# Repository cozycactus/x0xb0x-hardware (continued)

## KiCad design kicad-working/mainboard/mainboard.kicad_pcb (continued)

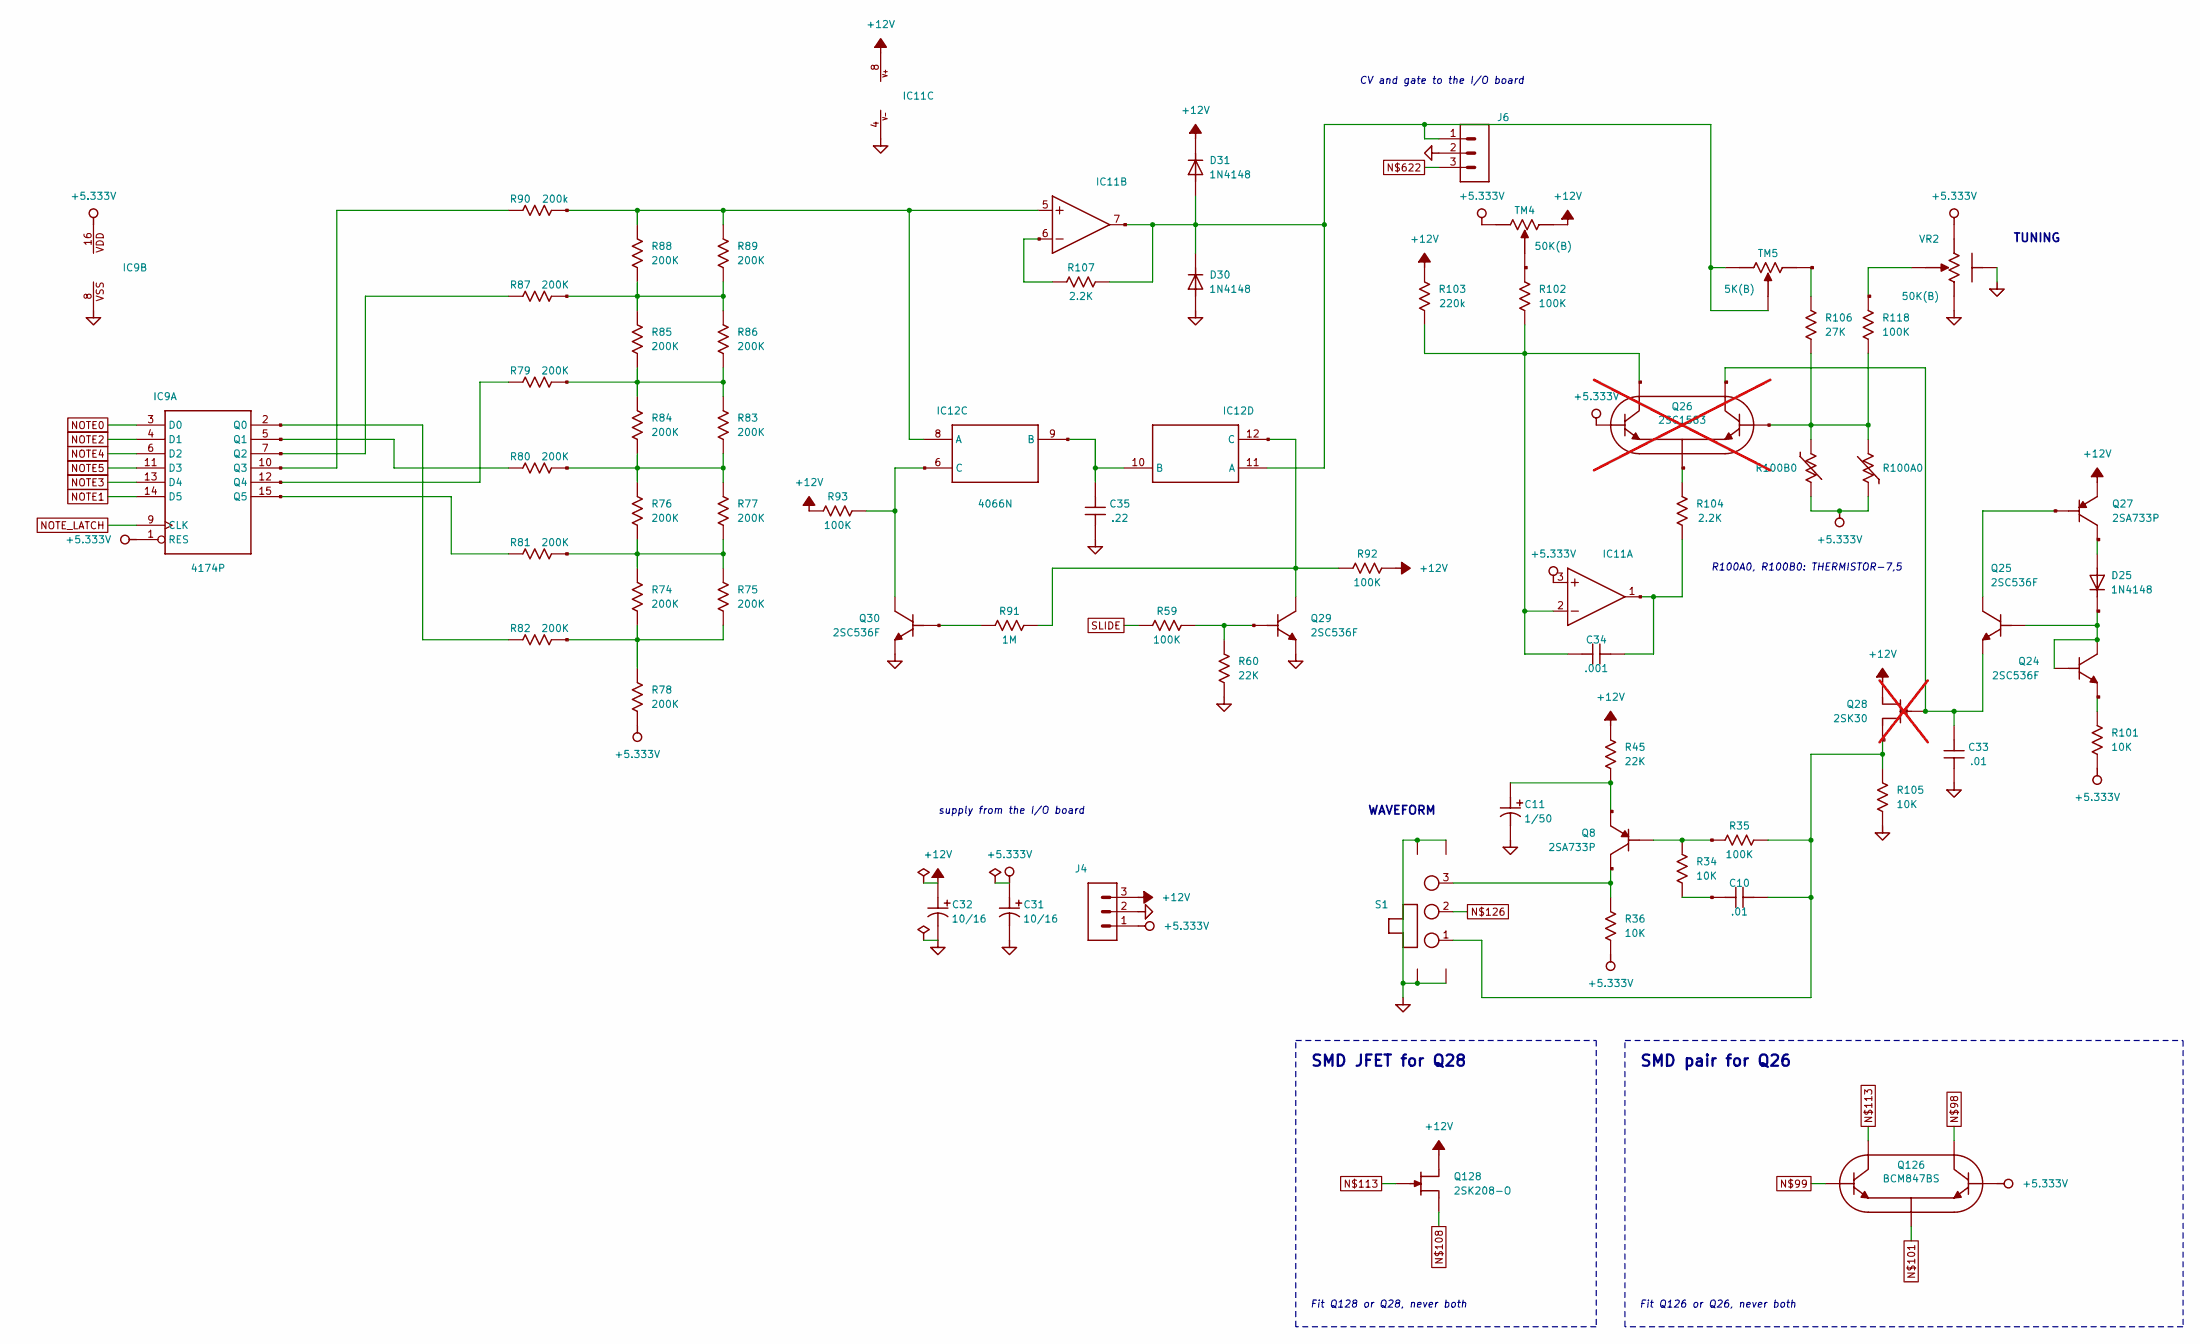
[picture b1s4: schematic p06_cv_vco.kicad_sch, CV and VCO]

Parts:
C10, C33: .01; C050-024X044
C11: 1/50; E5-6
C31, C32: 10/16; E5-6
C34: .001; C050-035X075
C35: .22; C050-045X075
D25, D30, D31: 1N4148; DO35-10
IC9: 4174P; DIL16
IC11: AN656N; DIL08
IC12: 4066N; DIL14
J4, J6: MA03-''; MA03-1
Q8, Q27: 2SA733P; TO92
Q24, Q25, Q29, Q30: 2SC536F
Q26: 2SC1583; SSIP5; not fitted
Q28: 2SK30; not fitted
Q126: BCM847BS; SOT-363_Hand
Q128: 2SK208-O; SC-59_Hand
R34, R36, R101, R105: 10K; 0207_5V
R35, R59, R92, R93, R102, R118: 100K; 0207_5V
R45, R60: 22K; 0207_5V
R74, R75, R76, R77, R78, R79, R80, R81, R82, R83, R84, R85, R86, R87, R88, R89: 200K; 0207_5V
R90: 200k; 0207_5V
R91: 1M; 0207_5V
R100A0, R100B0: THERMISTOR-7,5; R-7,5
R103: 220k; 0207_5V
R104, R107: 2.2K; 0207_5V
R106: 27K; 0207_5V
S1: SWITCH_GND; NKKTOGGLE
TM4: 50K(B); 306
TM5: 5K(B); 306
VR2: 50K(B); EVU

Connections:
+5.333V: C31.+, IC9.1 (RES), IC9.16 (VDD), IC11.3 (+IN), J4.1, Q26.1 (B), Q126.2 (B1), R36.2, R78.1, R100A0.2, R100B0.1, R101.2, TM4.3 (E), VR2.3 (E); also elsewhere on the board
+12V: C32.+, D31.C, IC11.8 (V+), J4.3, Q27.3 (E), Q28.1 (D), Q128.2 (D), R45.1, R92.2, R93.1, R103.1, TM4.1 (A); also elsewhere on the board
GND: C11.-, C31.-, C32.-, C33.2, C35.2, D30.A, IC9.8 (VSS), IC11.4 (V-), J4.2, J6.2, Q29.3 (E), Q30.3 (E), R60.1, R105.1, S1.M1, S1.M2, S1.M3, S1.M4, VR2.1 (A), VR2.M1, VR2.M2; also elsewhere on the board
unnamed: IC9.10 (Q3), R90.1
unnamed: C35.1, IC12.9 (B), IC12.10 (B)
unnamed: IC12.6 (C), Q30.2 (C), R93.2
unnamed: Q30.1 (B), R91.2
unnamed: IC11.6 (-IN), R107.1
unnamed: R85.2, R86.1, R87.2, R88.2, R89.1
unnamed: IC12.12 (C), Q29.2 (C), R91.1, R92.1
unnamed: R79.1, R83.1, R84.2, R85.1, R86.2
unnamed: IC9.15 (Q5), R81.2
unnamed: IC9.2 (Q0), R82.1
unnamed: IC9.12 (Q4), R79.2
unnamed: Q29.1 (B), R59.2, R60.2
unnamed: C34.1, IC11.1 (OUT), R104.2
unnamed: C34.2, IC11.2 (-IN), Q26.2 (C), Q126.6 (C1), R102.1, R103.2
unnamed: Q26.5 (B1), Q126.5 (B), R100A0.1, R100B0.2, R106.2, R118.2
unnamed: Q26.3 (E), Q126.1 (E), Q126.4 (E1), R104.1
unnamed: R118.1, VR2.2 (S)
unnamed: D25.A, Q27.2 (C)
unnamed: D25.C, Q24.1 (B), Q24.2 (C), Q25.1 (B)
unnamed: Q24.3 (E), R101.1
unnamed: Q25.2 (C), Q27.1 (B)
unnamed: C10.1, Q28.3 (S), Q128.1 (S), R35.1, R105.2, S1.1
unnamed: Q8.1 (B), R34.1, R35.2
unnamed: C10.2, R34.2
unnamed: IC11.5 (+IN), IC12.8 (A), R88.1, R89.2, R90.2
unnamed: C33.1, Q25.3 (E), Q26.4 (C1), Q28.2 (G), Q126.3 (C), Q128.3 (G)
unnamed: R102.2, TM4.2 (S)
unnamed 125: S1.2; also elsewhere on the board
unnamed: R76.2, R77.1, R80.2, R83.2, R84.1
unnamed: R106.1, TM5.1 (A)
unnamed: IC9.7 (Q2), R87.1
unnamed: IC9.5 (Q1), R80.1
unnamed: R74.2, R75.2, R78.2, R82.2
unnamed: R74.1, R75.1, R76.1, R77.2, R81.1
unnamed: C11.+, Q8.3 (E), R45.2
unnamed: Q8.2 (C), R36.1, S1.3
unnamed 297: J6.3; also elsewhere on the board
unnamed: D30.C, D31.A, IC11.7 (OUT), IC12.11 (A), J6.1, R107.2, TM5.2 (S), TM5.3 (E)
NOTE0: IC9.3 (D0); also elsewhere on the board
NOTE1: IC9.14 (D5); also elsewhere on the board
NOTE2: IC9.4 (D1); also elsewhere on the board
NOTE3: IC9.13 (D4); also elsewhere on the board
NOTE4: IC9.6 (D2); also elsewhere on the board
NOTE5: IC9.11 (D3); also elsewhere on the board
NOTE_LATCH: IC9.9 (CLK); also elsewhere on the board
SLIDE: R59.1; also elsewhere on the board

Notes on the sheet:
TUNING
R100A0, R100B0: THERMISTOR-7,5
WAVEFORM
supply from the I/O board
CV and gate to the I/O board
SMD pair for Q26
Fit Q126 or Q26, never both
SMD JFET for Q28
Fit Q128 or Q28, never both

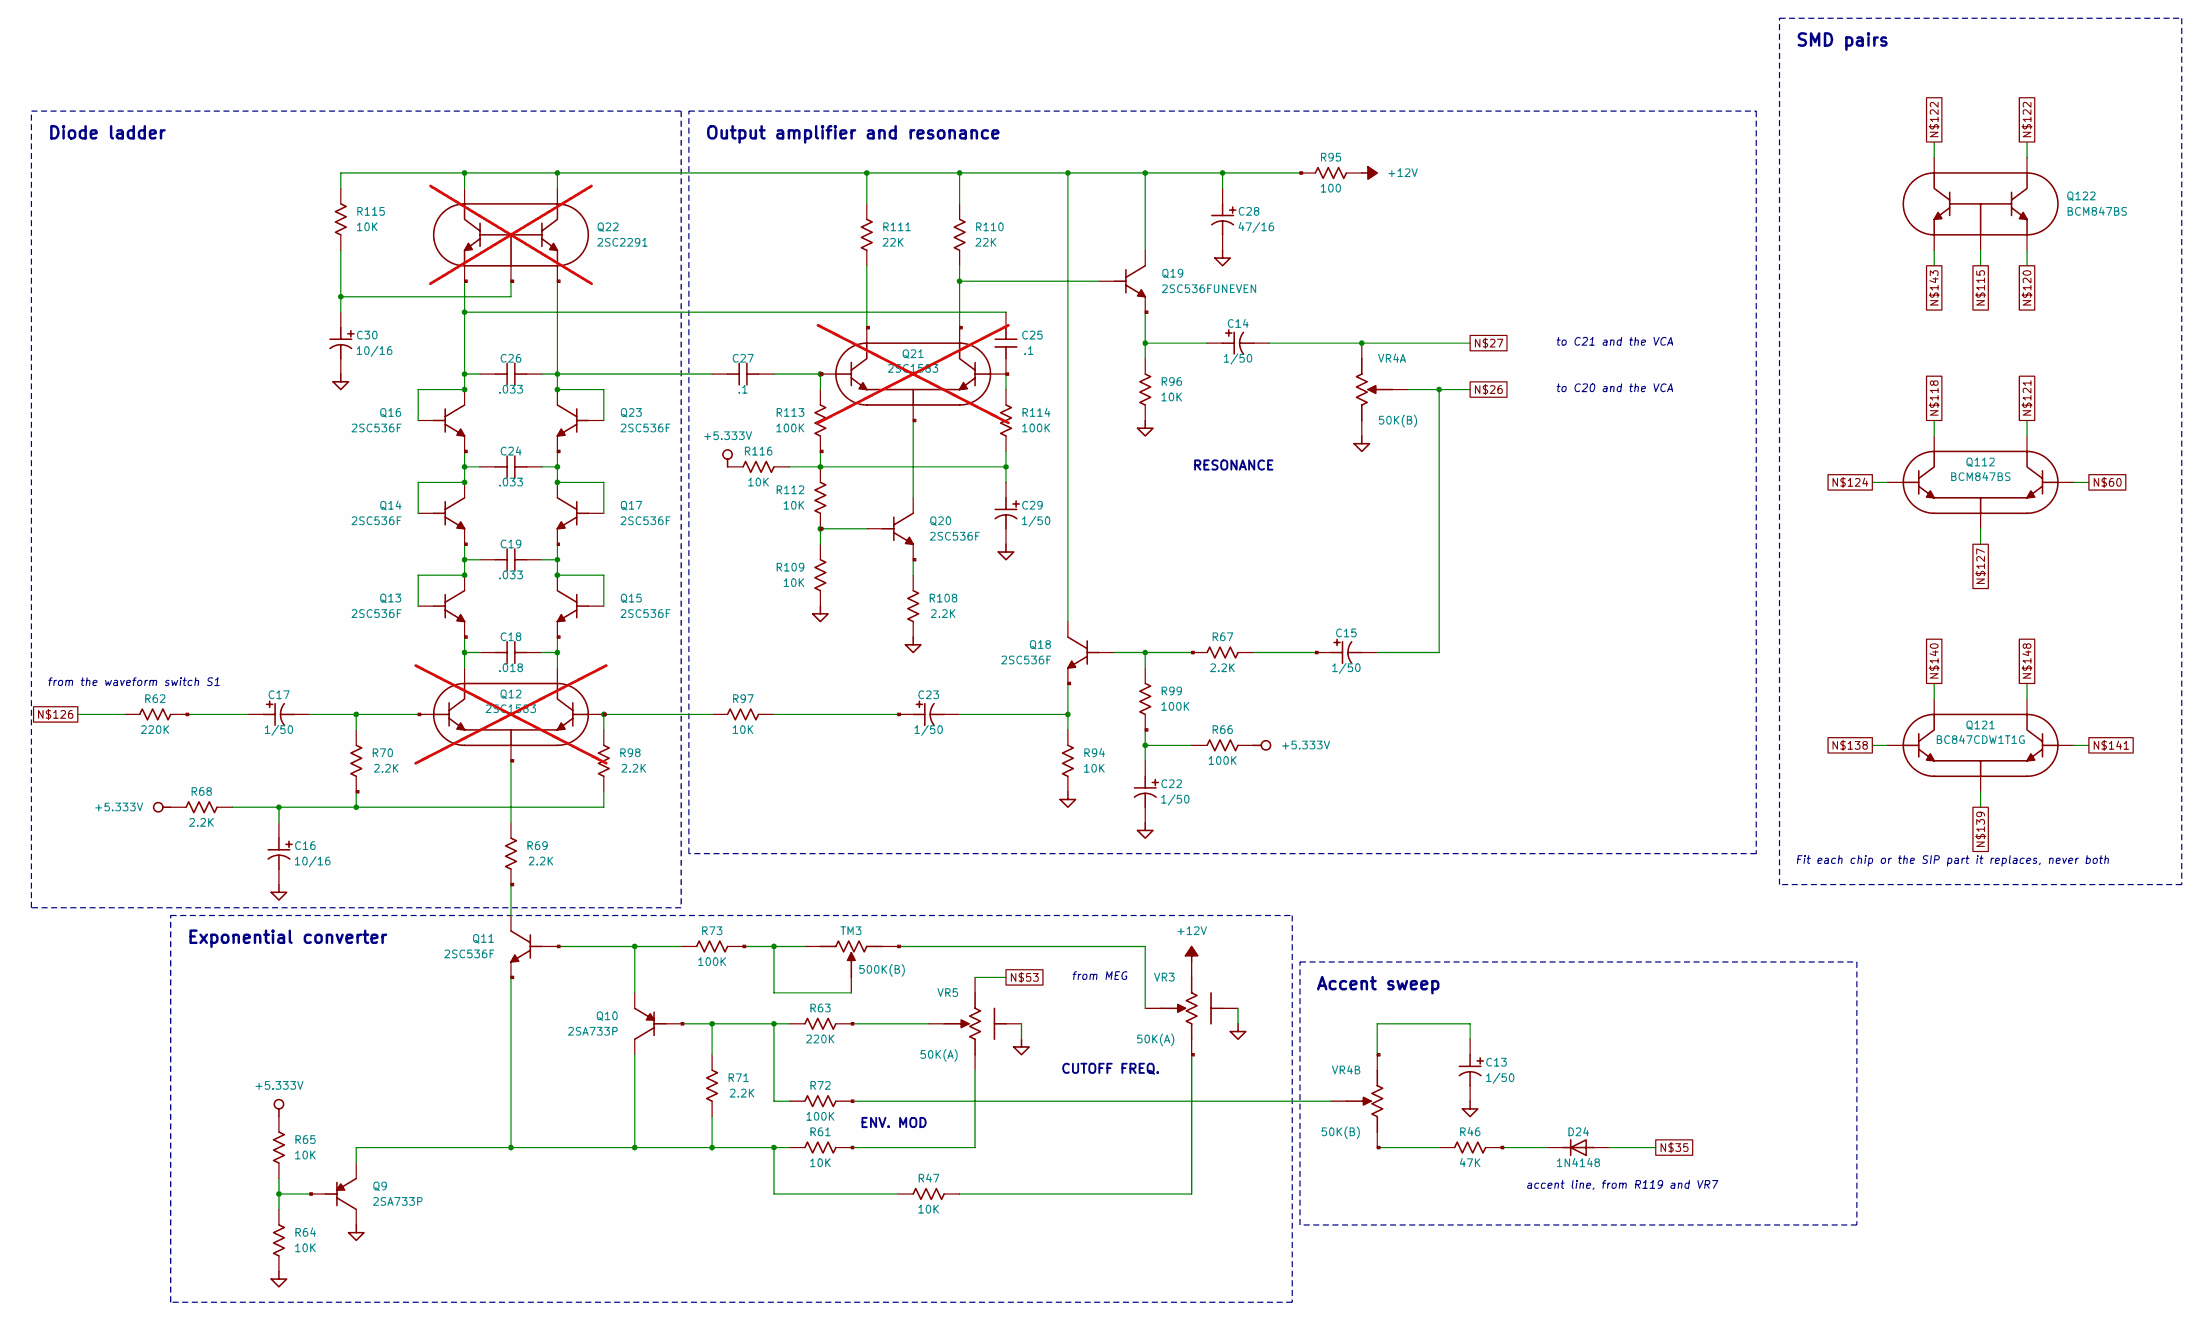
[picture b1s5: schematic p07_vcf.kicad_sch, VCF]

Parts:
C13, C14, C15, C22, C23, C29: 1/50; E5-6
C16, C30: 10/16; E5-6
C17: 1/50; E3,5-8
C18: .018; C050-025X075
C19, C24: .033; C050-025X075
C25, C27: .1; C050-030X075
C26: .033; C075-032X103
C28: 47/16; E5-6
D24: 1N4148; DO35-10
Q9, Q10: 2SA733P; TO92
Q11, Q13, Q14, Q15, Q16, Q18, Q20: 2SC536F
Q12, Q21: 2SC1583; SSIP5; not fitted
Q17, Q23: 2SC536F; 2SC536_UNEVEN
Q19: 2SC536FUNEVEN; 2SC536_UNEVEN
Q22: 2SC2291; SSIP5; not fitted
Q112, Q122: BCM847BS; SOT-363_Hand
Q121: BC847CDW1T1G; SOT-363_Hand
R46: 47K; 0207_5V
R47, R61, R64, R65, R94, R109, R112, R116: 10K; 0207_5V
R62, R63: 220K; 0207_5V
R66, R72, R73, R99, R113, R114: 100K; 0207_5V
R67, R68, R69, R70, R71, R108: 2.2K; 0207_5V
R95: 100; 0207_5V
R96, R97, R115: 10K; 0207_2V
R98: 2.2K; 0207_2V
R110, R111: 22K; 0207_5V
TM3: 500K(B); 306
VR3, VR5: 50K(A); EVU
VR4: 50K(B); ALPHADUAL

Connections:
+5.333V: R65.2, R66.2, R68.1, R116.2; also elsewhere on the board
+12V: R95.2, VR3.3 (E); also elsewhere on the board
GND: C13.-, C16.-, C22.-, C28.-, C29.-, C30.-, Q9.2 (C), R64.2, R94.1, R96.1, R108.1, R109.2, VR3.M1, VR3.M2, VR4.1A (A), VR4.M1 (MT1), VR4.M2 (MT2), VR5.M1, VR5.M2; also elsewhere on the board
unnamed 40: C15.-, VR4.2A (S); also elsewhere on the board
unnamed 41: C14.-, VR4.3A (E); also elsewhere on the board
unnamed 49: D24.A; also elsewhere on the board
unnamed: R61.1, VR5.1 (A)
unnamed 66: VR5.3 (E); also elsewhere on the board
unnamed: Q12.5 (B1), Q112.2 (B1), R97.1, R98.1
unnamed: C30.+, Q22.3 (B), Q122.2 (B), Q122.5 (B1), R115.2
unnamed: C24.1, Q14.1 (B), Q14.2 (C), Q16.3 (E)
unnamed: C19.1, Q13.1 (B), Q13.2 (C), Q14.3 (E)
unnamed: C18.2, Q12.2 (C), Q13.3 (E), Q112.3 (C)
unnamed: C24.2, Q17.1 (B), Q17.2 (C), Q23.3 (E)
unnamed: C26.2, C27.1, Q22.5 (E), Q23.1 (B), Q23.2 (C), Q122.1 (E)
unnamed: C18.1, Q12.4 (C1), Q15.3 (E), Q112.6 (C1)
unnamed: C28.+, Q18.2 (C), Q19.2 (C), Q22.2 (C1), Q22.4 (C), Q122.3 (C1), Q122.6 (C), R95.1, R110.2, R111.1, R115.1
unnamed: C17.+, R62.2
unnamed: C17.-, Q12.1 (B), Q112.5 (B), R70.1
unnamed: C16.+, R68.2, R70.2, R98.2
unnamed 125: R62.1; also elsewhere on the board
unnamed: Q12.3 (E), Q112.1 (E), Q112.4 (E1), R69.1
unnamed: C23.+, R97.2
unnamed: C23.-, Q18.3 (E), R94.2
unnamed: Q18.1 (B), R67.2, R99.2
unnamed: C22.+, R66.1, R99.1
unnamed: C15.+, R67.1
unnamed: Q10.1 (B), R63.1, R71.2, R72.1
unnamed: Q20.1 (B), R109.1, R112.2
unnamed: Q20.3 (E), R108.2
unnamed: C25.2, Q21.1 (B), Q121.5 (B), R114.2
unnamed: Q20.2 (C), Q21.3 (E), Q121.1 (E), Q121.4 (E1)
unnamed: Q19.1 (B), Q21.2 (C), Q121.3 (C), R110.1
unnamed: C27.2, Q21.5 (B1), Q121.2 (B1), R113.1
unnamed: R47.1, VR3.1 (A)
unnamed: C25.1, C26.1, Q16.1 (B), Q16.2 (C), Q22.1 (E1), Q122.4 (E1)
unnamed: C14.+, Q19.3 (E), R96.2
unnamed: Q11.2 (C), R69.2
unnamed: Q10.3 (E), Q11.1 (B), R73.1
unnamed: Q21.4 (C1), Q121.6 (C1), R111.2
unnamed: Q9.1 (B), R64.1, R65.1
unnamed: R73.2, TM3.2 (S), TM3.3 (E)
unnamed: R72.2, VR4.2B (S1)
unnamed: R63.2, VR5.2 (S)
unnamed: TM3.1 (A), VR3.2 (S)
unnamed: D24.C, R46.1
unnamed: R46.2, VR4.1B (A1)
unnamed: C13.+, VR4.3B (E1)
unnamed: Q9.3 (E), Q10.2 (C), Q11.3 (E), R47.2, R61.2, R71.1
unnamed: C29.+, R112.1, R113.2, R114.1, R116.1
Q17: C19.2, Q15.1 (B), Q15.2 (C), Q17.3 (E)

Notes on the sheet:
Diode ladder
Output amplifier and resonance
Exponential converter
Accent sweep
from the waveform switch S1
to C21 and the VCA
to C20 and the VCA
RESONANCE
from MEG
ENV. MOD
CUTOFF FREQ.
accent line, from R119 and VR7
SMD pairs
Fit each chip or the SIP part it replaces, never both

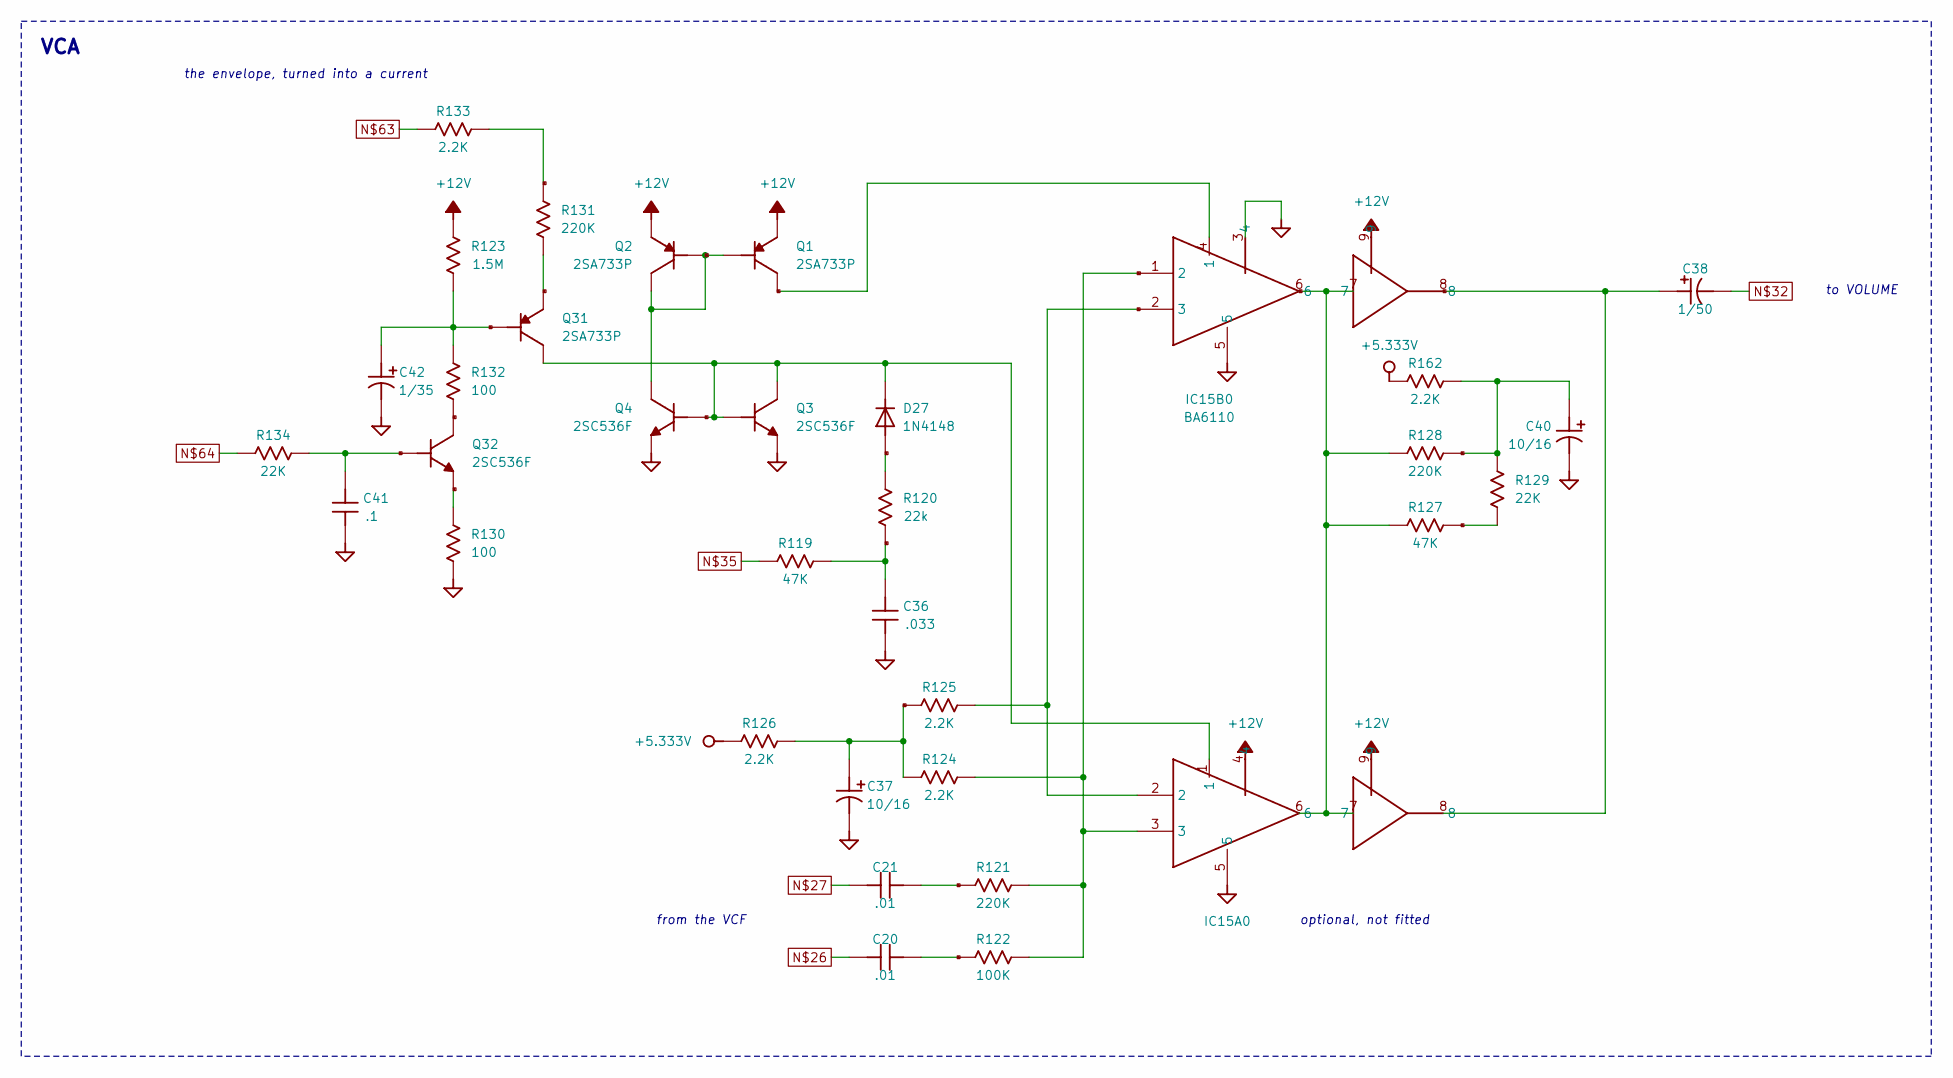
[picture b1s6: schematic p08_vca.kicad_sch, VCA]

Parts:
C20, C21: .01; C050-024X044
C36: .033; C050-025X075
C37, C40: 10/16; E5-6
C38: 1/50; E5-6
C41: .1; C050-030X075
C42: 1/35; E2,5-7
D27: 1N4148; DO35-10
IC15A0: BA662''; SIP9
IC15B0: BA6110; SIP9
Q1, Q2, Q31: 2SA733P; TO92
Q3, Q4, Q32: 2SC536F
R119, R127: 47K; 0207_5V
R120: 22k; 0207_5V
R121, R128, R131: 220K; 0207_5V
R122: 100K; 0207_5V
R123: 1.5M; 0207_5V
R124, R125, R126, R133, R162: 2.2K; 0207_5V
R129, R134: 22K; 0207_5V
R130, R132: 100; 0207_5V

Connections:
+5.333V: R126.1, R162.1; also elsewhere on the board
+12V: IC15A0.4, IC15A0.9, IC15B0.9, Q1.3 (E), Q2.3 (E), R123.2; also elsewhere on the board
GND: C36.2, C37.-, C40.-, C41.2, C42.-, IC15A0.5, IC15B0.3 (4), IC15B0.5, Q3.3 (E), Q4.3 (E), R130.2; also elsewhere on the board
unnamed: C20.1, R122.2
unnamed: C37.+, R124.2, R125.1, R126.2
unnamed: IC15A0.2, IC15B0.2 (3), R125.2
unnamed: C21.1, R121.1
unnamed 40: C20.2; also elsewhere on the board
unnamed 41: C21.2; also elsewhere on the board
unnamed: IC15A0.6, IC15A0.7, IC15B0.6, IC15B0.7, R127.1, R128.2
unnamed: IC15B0.4 (1), Q1.2 (C)
unnamed: R127.2, R129.1
unnamed: C40.+, R128.1, R129.2, R162.2
unnamed 46: C38.-; also elsewhere on the board
unnamed: D27.A, R120.1
unnamed: C36.1, R119.1, R120.2
unnamed 49: R119.2; also elsewhere on the board
unnamed: C38.+, IC15A0.8, IC15B0.8
unnamed: Q32.3 (E), R130.1
unnamed 73: R133.2; also elsewhere on the board
unnamed 74: R134.1; also elsewhere on the board
unnamed: C41.1, Q32.1 (B), R134.2
unnamed: Q32.2 (C), R132.2
unnamed: C42.+, Q31.1 (B), R123.1, R132.1
unnamed: D27.C, IC15A0.1, Q3.1 (B), Q3.2 (C), Q4.1 (B), Q31.2 (C)
unnamed: Q31.3 (E), R131.1
unnamed: R131.2, R133.1
unnamed: Q1.1 (B), Q2.1 (B), Q2.2 (C), Q4.2 (C)
unnamed: IC15A0.3, IC15B0.1 (2), R121.2, R122.1, R124.1

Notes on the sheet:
VCA
the envelope, turned into a current
optional, not fitted
to VOLUME
from the VCF

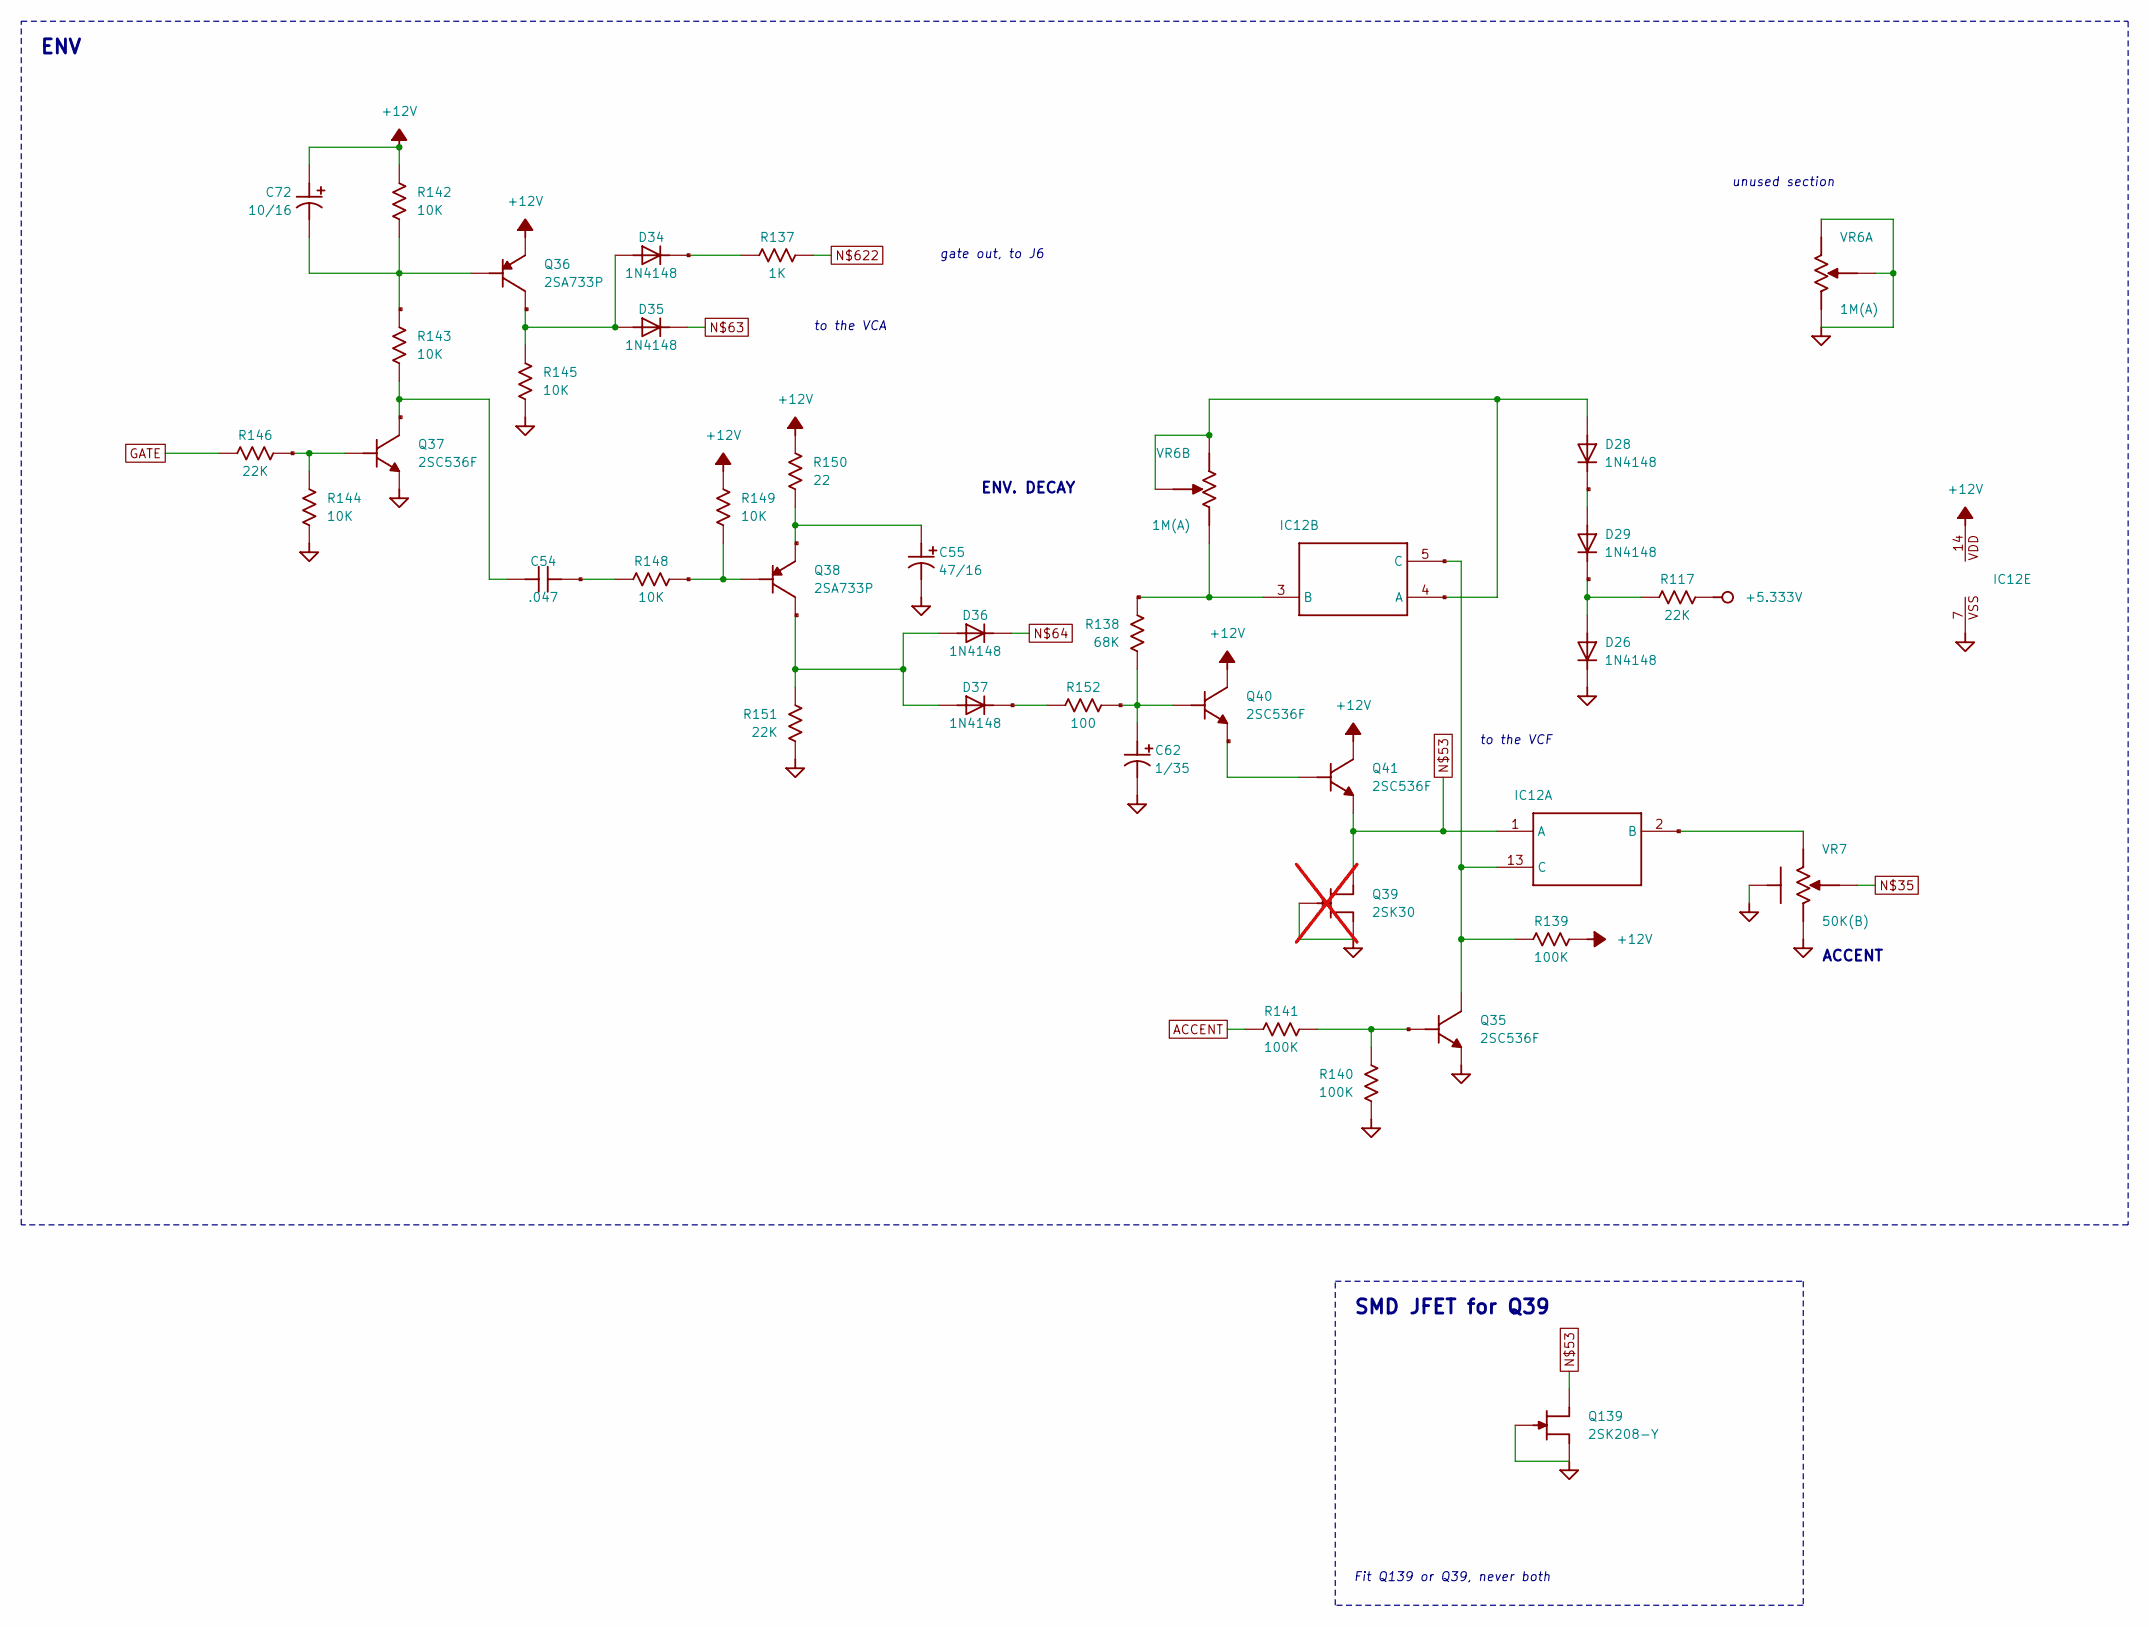
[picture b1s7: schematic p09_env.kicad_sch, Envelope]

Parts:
C54: .047; C050-055X075
C55: 47/16; E5-6
C62: 1/35; E2,5-7
C72: 10/16; E5-6
D26, D28, D29, D34, D35, D36, D37: 1N4148; DO35-10
IC12: 4066N; DIL14
Q35, Q37, Q40, Q41: 2SC536F
Q36, Q38: 2SA733P; TO92
Q39: 2SK30; not fitted
Q139: 2SK208-Y; SC-59_Hand
R117, R146, R151: 22K; 0207_5V
R137: 1K; 0207_10
R138: 68K; 0207_5V
R139, R140, R141: 100K; 0207_5V
R142, R143, R144, R145, R148, R149: 10K; 0207_5V
R150: 22; 0207_5V
R152: 100; 0207_5V
VR6: 1M(A); ALPHADUAL
VR7: 50K(B); EVU

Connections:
+5.333V: R117.1; also elsewhere on the board
+12V: C72.+, IC12.14 (VDD), Q36.3 (E), Q40.2 (C), Q41.2 (C), R139.2, R142.2, R149.2, R150.1; also elsewhere on the board
ACCENT: R141.2; also elsewhere on the board
GATE: R146.2; also elsewhere on the board
GND: C55.-, C62.-, D26.C, IC12.7 (VSS), Q35.3 (E), Q37.3 (E), Q39.2 (G), Q39.3 (S), Q139.1 (S), Q139.3 (G), R140.2, R144.2, R145.1, R151.1, VR6.1A (A), VR6.2A (S), VR6.3A (E), VR6.M1 (MT1), VR6.M2 (MT2), VR7.1 (A), VR7.M1, VR7.M2; also elsewhere on the board
unnamed 49: VR7.2 (S); also elsewhere on the board
unnamed: C55.+, Q38.3 (E), R150.2
unnamed: C72.-, Q36.1 (B), R142.1, R143.2
unnamed: D34.A, D35.A, Q36.2 (C), R145.2
unnamed: Q38.1 (B), R148.2, R149.1
unnamed: D37.C, R152.2
unnamed: C54.1, R148.1
unnamed: C54.2, Q37.2 (C), R143.1
unnamed: Q37.1 (B), R144.1, R146.1
unnamed: D36.A, D37.A, Q38.2 (C), R151.2
unnamed: C62.+, Q40.1 (B), R138.2, R152.1
unnamed: Q40.3 (E), Q41.1 (B)
unnamed: D26.A, D29.C, R117.2
unnamed: D28.C, D29.A
unnamed: D28.A, IC12.4 (A), VR6.2B (S1), VR6.3B (E1)
unnamed 66: IC12.1 (A), Q39.1 (D), Q41.3 (E), Q139.2 (D); also elsewhere on the board
unnamed: Q35.1 (B), R140.1, R141.1
unnamed: IC12.5 (C), IC12.13 (C), Q35.2 (C), R139.1
unnamed: D34.C, R137.1
unnamed 73: D35.C; also elsewhere on the board
unnamed 74: D36.C; also elsewhere on the board
unnamed: IC12.2 (B), VR7.3 (E)
unnamed: IC12.3 (B), R138.1, VR6.1B (A1)
unnamed 297: R137.2; also elsewhere on the board

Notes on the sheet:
ENV
gate out, to J6
to the VCA
ENV. DECAY
unused section
to the VCF
ACCENT
SMD JFET for Q39
Fit Q139 or Q39, never both

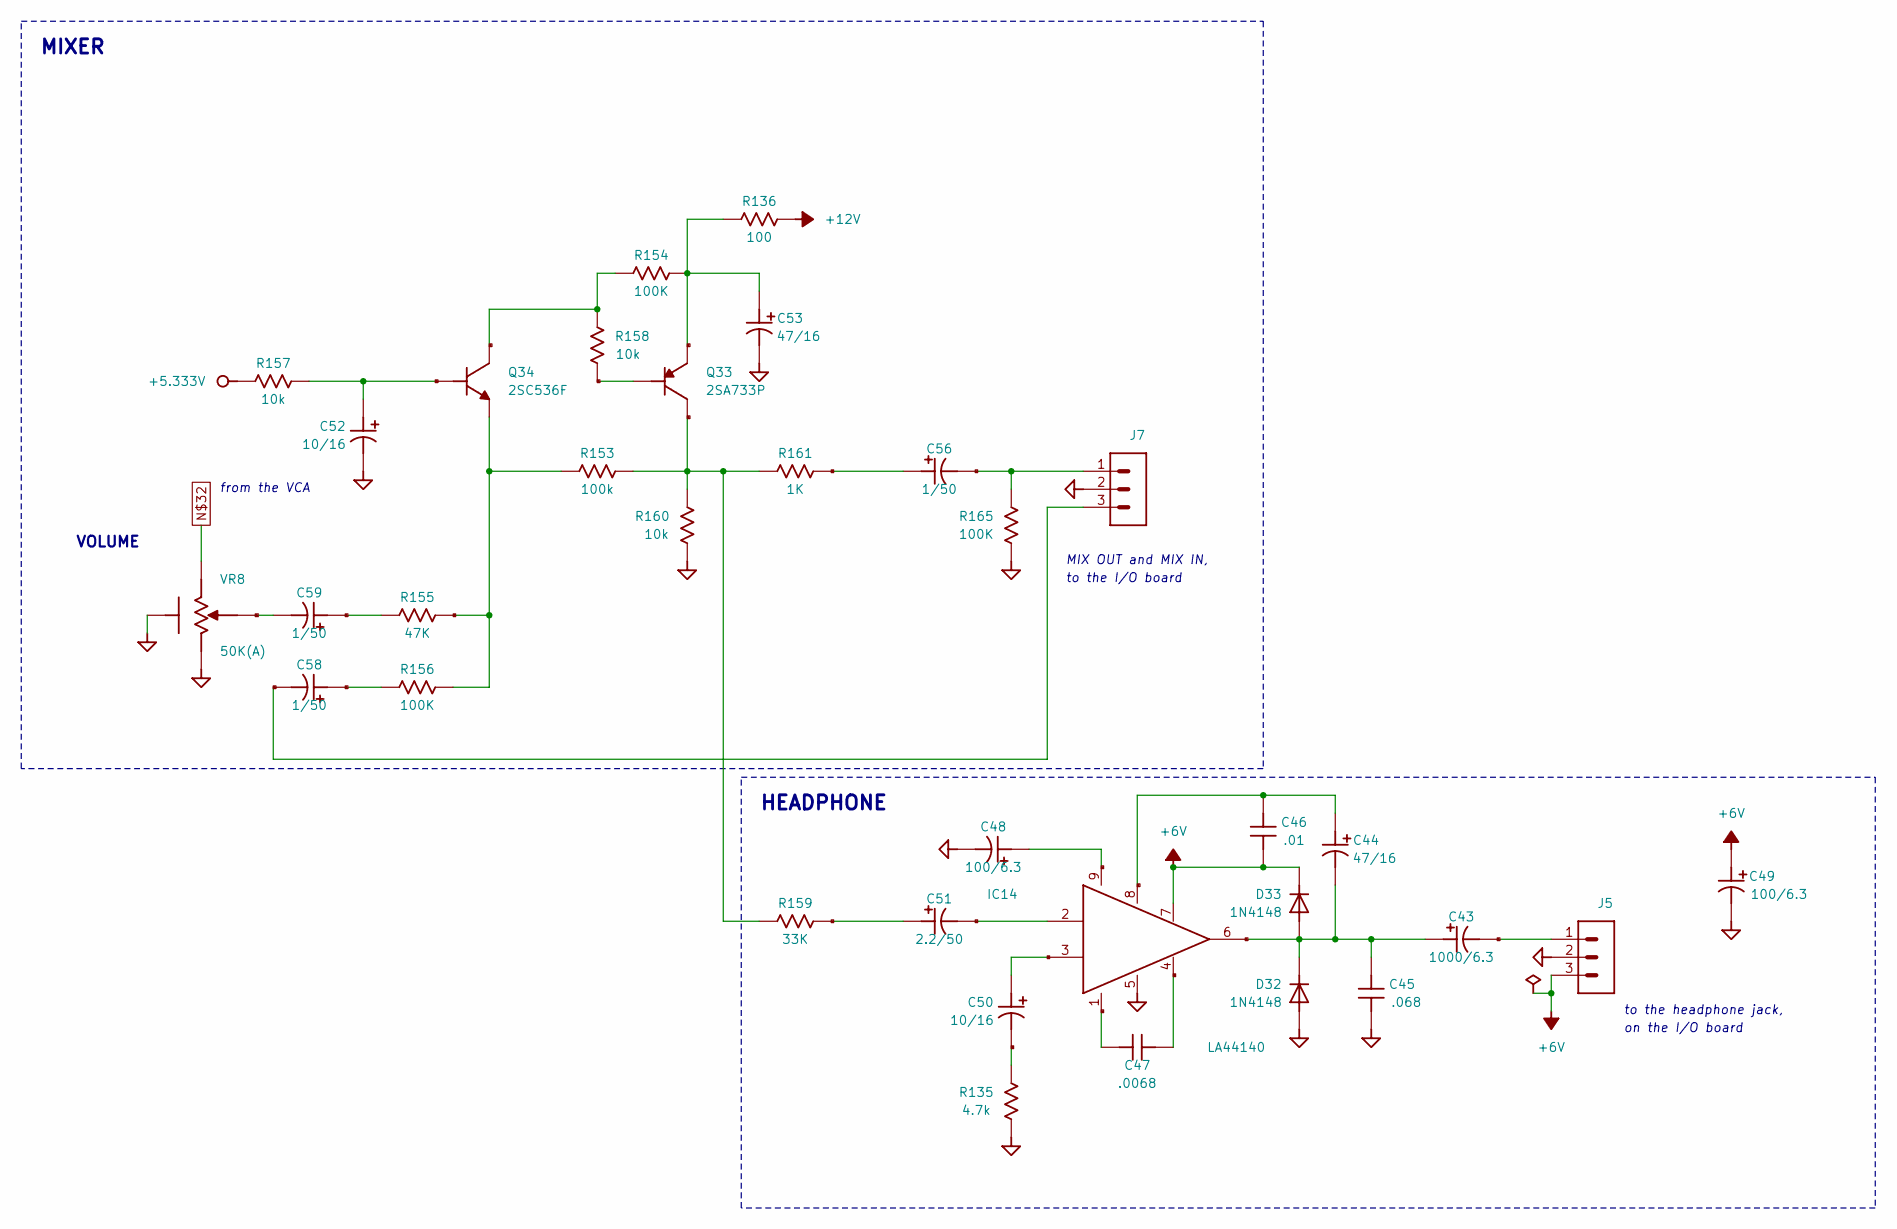
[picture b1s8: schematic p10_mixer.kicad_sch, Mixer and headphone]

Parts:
C43: 1000/6.3; E5-5
C44, C53: 47/16; E5-6
C45: .068; C050-050X075
C46: .01; C050-024X044
C47: .0068; C050-075X075
C48, C49: 100/6.3; E5-6
C50, C52: 10/16; E5-6
C51: 2.2/50; E5-6
C56, C58, C59: 1/50; E5-6
D32, D33: 1N4148; DO35-10
IC14: LA44140; SIP9
J5, J7: MA03-''; MA03-1
Q33: 2SA733P; TO92
Q34: 2SC536F
R135: 4.7k; 0207_5V
R136: 100; 0207_5V
R153: 100k; 0207_5V
R154, R156, R165: 100K; 0207_5V
R155: 47K; 0207_5V
R157, R158, R160: 10k; 0207_5V
R159: 33K; 0207_5V
R161: 1K; 0207_5V
VR8: 50K(A); EVU

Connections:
+5.333V: R157.2; also elsewhere on the board
+6V: C46.1, C49.+, D33.C, IC14.7, J5.3
+12V: R136.1; also elsewhere on the board
C48: C48.+, IC14.9
GND: C45.2, C48.-, C49.-, C52.-, C53.-, D32.A, IC14.5, J5.2, J7.2, R135.1, R160.1, R165.2, VR8.1 (A), VR8.M1, VR8.M2; also elsewhere on the board
unnamed: C51.-, IC14.2
unnamed: C51.+, R159.1
unnamed: C50.+, IC14.3
unnamed: C50.-, R135.2
unnamed: Q34.3 (E), R153.1, R155.2, R156.1
unnamed: C56.+, R161.1
unnamed: C56.-, J7.1, R165.1
unnamed: C47.1, IC14.4
unnamed: C47.2, IC14.1
unnamed: C43.-, J5.1
unnamed: C43.+, C44.-, C45.1, D32.C, D33.A, IC14.6
unnamed: Q33.2 (C), R153.2, R159.2, R160.2, R161.2
unnamed: C44.+, C46.2, IC14.8
unnamed: Q34.2 (C), R154.1, R158.1
unnamed: Q33.1 (B), R158.2
unnamed: C53.+, Q33.3 (E), R136.2, R154.2
unnamed: C52.+, Q34.1 (B), R157.1
unnamed: C59.+, R155.1
unnamed: C58.+, R156.2
unnamed: C58.-, J7.3
unnamed 46: VR8.3 (E); also elsewhere on the board
unnamed: C59.-, VR8.2 (S)

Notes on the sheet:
MIXER
HEADPHONE
from the VCA
VOLUME
MIX OUT and MIX IN,
to the I/O board
to the headphone jack,
on the I/O board
